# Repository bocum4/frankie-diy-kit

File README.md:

# frankie-diy-kit
Related hardware and building files. 

NOTA IMPORTANTE:

LIMITACIÓN DE GARANTÍA.

Este es un proyecto de dificultad media a avanzada. Se sugiere encarecidamente el previo conocimiento en el código de resistencias y otros elementos electrónicos así como experiencia soldando con cautín y soldadura de estaño. Bocuma no se responsabiliza por cualquier daño personal o material, defecto o malfunción derivada del incorrecto ensamble del kit.

Si tuviste problemas al armar tu kit y este no funciona después de haberlo ensamblado y verificado la guia de ensamble y guía de usuario, podremos asesorarte sin costo siempre y cuando esta revisión se realice durante los 30 días naturales siguientes a la fecha de tu compra. Transcurrido este lapso de tiempo las revisiones incurren en honorarios y están sujetas a nuestra disponibilidad y según nuestra carga de trabajo. Ponte en contacto con nosotros en contacto@bocuma.mx 

Todos nuestros kits están garantizados por nuestros proveedores, si por alguna razón algún componente de tu kit presenta una falla de fábrica lo reemplazaremos sin costo, para ello requeriremos que nos envies el componente o pieza defectuosa. Esta garantía tiene validez hasta por 3 meses después de la fecha de tu compra. Ponte en contacto con nosotros en contacto@bocuma.mx y te guiaremos en el proceso.

En caso de que a tu kit le falte una pieza o la hayas extraviado, puedes contactarnos en contacto@bocuma.mx y con gusto nos pondremos de acuerdo contigo para su reposición. Esta garantía tiene validez hasta por 3 meses después de la fecha de tu compra.

HACIA NUEVOS UNIVERSOS SONOROS | BOCUMA GDL MX 2021.

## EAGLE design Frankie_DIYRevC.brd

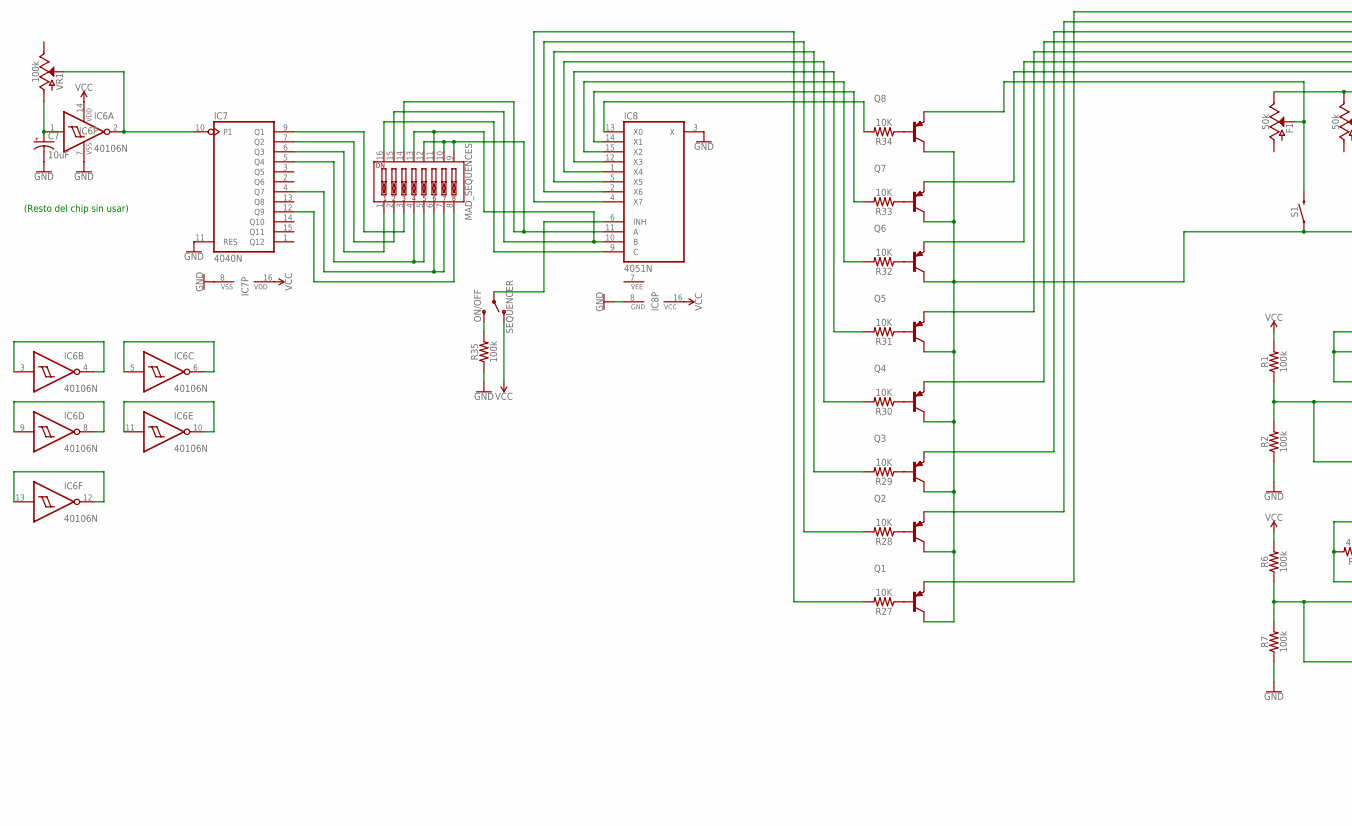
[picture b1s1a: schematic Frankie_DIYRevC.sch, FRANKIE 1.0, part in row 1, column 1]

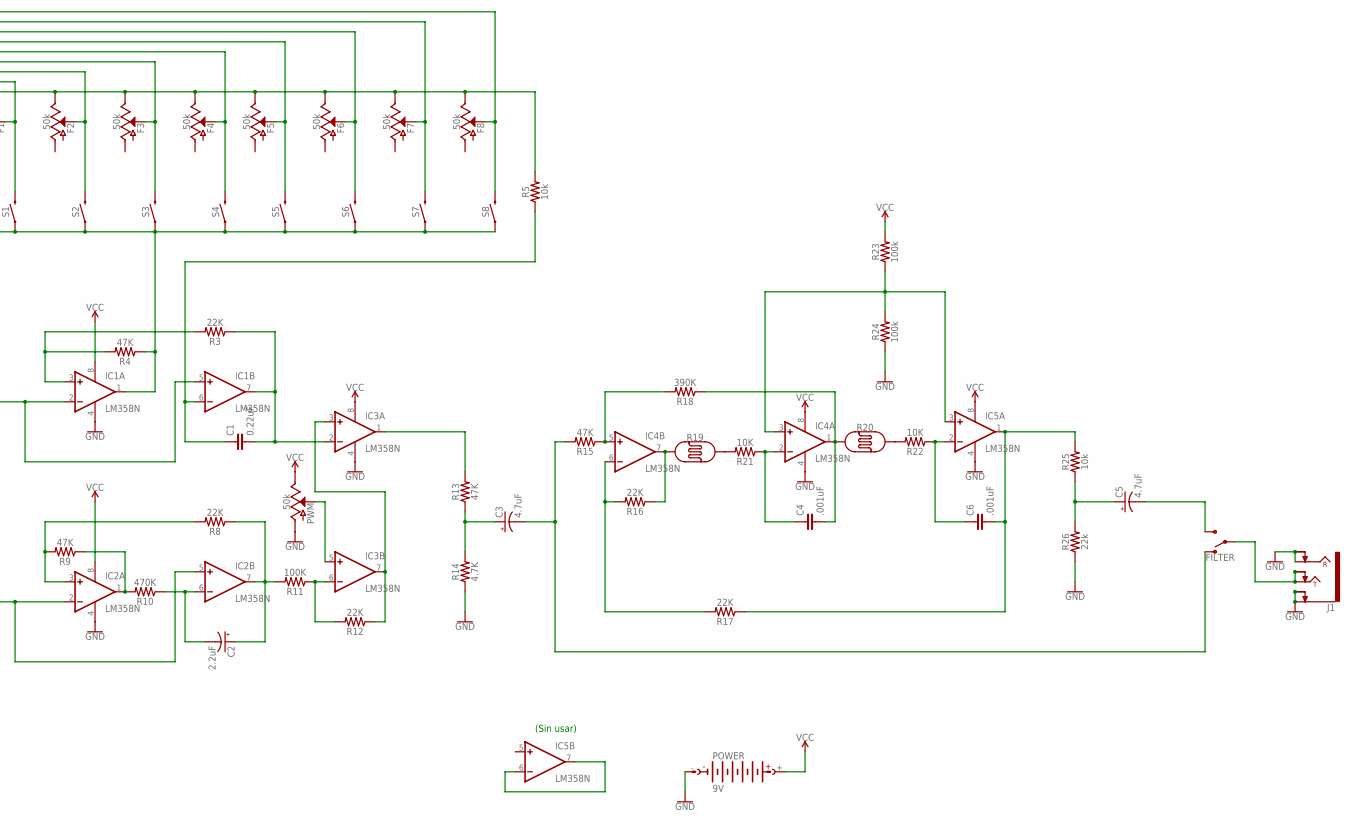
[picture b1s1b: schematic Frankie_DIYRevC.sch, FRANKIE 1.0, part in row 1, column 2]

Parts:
C1: 0.22uF; C5B2.5
C2: 2.2uF; CPOL-RADIAL-2.5MM-5MM-KIT
C3, C5: 4.7uF; CPOL-RADIAL-2.5MM-5MM-KIT
C4, C6: .001uF; C5B2.5
C7: 10uF; CPOL-RADIAL-2.5MM-5MM-KIT
F1, F2, F3, F4, F5, F6, F7, F8: 50k; POT-PTH-ALPS-KIT
FILTER: SWITCH-SPDT-PTH-11.6X4.0MM-KIT; SWITCH_SPDT_PTH_11.6X4.0MM_KIT
IC1, IC2, IC3, IC4, IC5: LM358N; DIL08
IC6: 40106N; DIL14
IC7: 4040N; DIL16
IC8: 4051N; DIL16
J1: AUDIO_JACK_TRS_0.25"_PTH_RA; AUDIO_JACK_0.25"_TRS_PTH_RA
MAD_SEQUENCES: DIP-08-PTH; DIPSWITCH-08
POWER: 9V; AB9V
PWM: 50k; POT-PTH-ALPS-KIT
Q1, Q2, Q3, Q4, Q5, Q6, Q7, Q8: 2N3906; TO92
R1, R2, R6, R7, R23, R24, R35: 100k; AXIAL-0.3
R3, R8, R12, R16, R17: 22K; AXIAL-0.3
R4, R9, R13, R15: 47K; AXIAL-0.3
R5, R25: 10k; AXIAL-0.3
R10: 470K; AXIAL-0.3
R11: 100K; AXIAL-0.3
R14: 4.7K; AXIAL-0.3
R18: 390K; AXIAL-0.3
R19, R20: PHOTOCELLPTH-KIT; PHOTOCELL-KIT
R21, R22, R27, R28, R29, R30, R31, R32, R33, R34: 10K; AXIAL-0.3
R26: 22k; AXIAL-0.3
S1, S2, S3, S4, S5, S6, S7, S8: MOMENTARY-SWITCH-SPST-PTH-12MM; TACTILE_SWITCH_PTH_12MM
SEQUENCER: ON/OFF; SWITCH_SPDT_PTH_11.6X4.0MM_KIT
VR1: 100k; POT-PTH-ALPS-KIT

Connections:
GND: C7.2 (-), IC1.4 (V-), IC2.4 (V-), IC3.4 (V-), IC4.4 (V-), IC5.4 (V-), IC6.7 (VSS), IC7.8 (VSS), IC7.11 (RES), IC8.3 (X), IC8.8 (GND), J1.RING, J1.RING-NORM, J1.SLEEVE (EARTH), J1.SLEEVE-NORM (EARTH-NORM), POWER.-, PWM.P$3 (A), R2.P$1 (1), R7.P$1 (1), R14.P$1 (1), R24.P$1 (1), R26.P$1 (1), R35.P$1 (1)
unnamed: IC1.2 (-IN), IC1.5 (+IN), R1.P$1 (1), R2.P$2 (2)
unnamed: C1.2, IC1.7 (OUT), IC3.2 (-IN), R3.P$1 (1)
unnamed: IC1.3 (+IN), R3.P$2 (2), R4.P$2 (2)
unnamed: C1.1, IC1.6 (-IN), R5.P$1 (1)
unnamed: IC1.1 (OUT), Q1.1 (C), Q2.1 (C), Q3.1 (C), Q4.1 (C), Q5.1 (C), Q6.1 (C), Q7.1 (C), Q8.1 (C), R4.P$1 (1), S1.1, S2.1, S3.1, S4.1, S5.1, S6.1, S7.1, S8.1
unnamed: F1.P$2 (S), Q8.3 (E), S1.3 (2)
unnamed: F2.P$2 (S), Q7.3 (E), S2.3 (2)
unnamed: IC7.5 (Q4), MAD_SEQUENCES.4, MAD_SEQUENCES.5
unnamed: F4.P$2 (S), Q5.3 (E), S4.3 (2)
unnamed: F5.P$2 (S), Q4.3 (E), S5.3 (2)
unnamed: F6.P$2 (S), Q3.3 (E), S6.3 (2)
unnamed: F7.P$2 (S), Q2.3 (E), S7.3 (2)
unnamed: F8.P$2 (S), Q1.3 (E), S8.3 (2)
unnamed: F1.P$1 (E), F2.P$1 (E), F3.P$1 (E), F4.P$1 (E), F5.P$1 (E), F6.P$1 (E), F7.P$1 (E), F8.P$1 (E), R5.P$2 (2)
unnamed: IC2.2 (-IN), IC2.5 (+IN), R6.P$1 (1), R7.P$2 (2)
unnamed: IC2.3 (+IN), R8.P$2 (2), R9.P$2 (2)
unnamed: IC2.1 (OUT), R9.P$1 (1), R10.P$2 (2)
unnamed: C2.2 (-), IC2.6 (-IN), R10.P$1 (1)
unnamed: IC3.6 (-IN), R11.P$1 (1), R12.P$2 (2)
unnamed: C2.1 (+), IC2.7 (OUT), R8.P$1 (1), R11.P$2 (2)
unnamed: IC3.5 (+IN), PWM.P$2 (S)
unnamed: IC3.3 (+IN), IC3.7 (OUT), R12.P$1 (1)
unnamed: IC3.1 (OUT), R13.P$2 (2)
unnamed: C3.1 (+), R13.P$1 (1), R14.P$2 (2)
unnamed: IC4.5 (+IN), R15.P$1 (1), R18.P$2 (2)
unnamed: C3.2 (-), FILTER.1 (O), R15.P$2 (2)
unnamed: IC4.6 (-IN), R16.P$2 (2), R17.P$2 (2)
unnamed: IC4.7 (OUT), R16.P$1 (1), R19.1
unnamed: C6.2, IC5.1 (OUT), R17.P$1 (1), R25.P$2 (2)
unnamed: C4.2, IC4.1 (OUT), R18.P$1 (1), R20.1
unnamed: R19.2, R21.P$2 (2)
unnamed: R20.2, R22.P$2 (2)
unnamed: C4.1, IC4.2 (-IN), R21.P$1 (1)
unnamed: C6.1, IC5.2 (-IN), R22.P$1 (1)
unnamed: IC5.6 (-IN), IC5.7 (OUT)
unnamed: IC4.3 (+IN), IC5.3 (+IN), R23.P$1 (1), R24.P$2 (2)
unnamed: C5.1 (+), R25.P$1 (1), R26.P$2 (2)
unnamed: FILTER.2, J1.TIP, J1.TIP-NORM
unnamed: Q1.2 (B), R27.P$1 (1)
unnamed: C5.2 (-), FILTER.3 (S)
unnamed: Q2.2 (B), R28.P$1 (1)
unnamed: Q3.2 (B), R29.P$1 (1)
unnamed: Q4.2 (B), R30.P$1 (1)
unnamed: Q5.2 (B), R31.P$1 (1)
unnamed: Q6.2 (B), R32.P$1 (1)
unnamed: Q7.2 (B), R33.P$1 (1)
unnamed: Q8.2 (B), R34.P$1 (1)
unnamed: C7.1 (+), IC6.1 (I), VR1.P$3 (A)
unnamed: IC6.2 (O), IC7.10 (P1), VR1.P$2 (S)
unnamed: IC7.9 (Q1), MAD_SEQUENCES.3
unnamed: IC7.12 (Q9), MAD_SEQUENCES.8
unnamed: IC7.6 (Q3), MAD_SEQUENCES.1
unnamed: IC8.11 (A), MAD_SEQUENCES.9, MAD_SEQUENCES.10, MAD_SEQUENCES.12, MAD_SEQUENCES.14
unnamed: IC8.10 (B), MAD_SEQUENCES.11, MAD_SEQUENCES.13, MAD_SEQUENCES.15
unnamed: IC8.9 (C), MAD_SEQUENCES.16
unnamed: IC8.6 (INH), SEQUENCER.2
unnamed: R35.P$2 (2), SEQUENCER.3 (S)
unnamed: IC8.13 (X0), R34.P$2 (2)
unnamed: IC8.14 (X1), R33.P$2 (2)
unnamed: IC8.15 (X2), R32.P$2 (2)
unnamed: IC8.12 (X3), R31.P$2 (2)
unnamed: IC8.1 (X4), R30.P$2 (2)
unnamed: IC8.5 (X5), R29.P$2 (2)
unnamed: IC8.2 (X6), R28.P$2 (2)
unnamed: IC8.4 (X7), R27.P$2 (2)
unnamed: IC7.7 (Q2), MAD_SEQUENCES.2
unnamed: IC7.4 (Q7), MAD_SEQUENCES.6, MAD_SEQUENCES.7
unnamed: F3.P$2 (S), Q6.3 (E), S3.3 (2)
unnamed: IC6.3 (I), IC6.4 (O)
unnamed: IC6.5 (I), IC6.6 (O)
unnamed: IC6.8 (O), IC6.9 (I)
unnamed: IC6.10 (O), IC6.11 (I)
unnamed: IC6.12 (O), IC6.13 (I)
VCC: IC1.8 (V+), IC2.8 (V+), IC3.8 (V+), IC4.8 (V+), IC5.8 (V+), IC6.14 (VDD), IC7.16 (VDD), IC8.16 (VCC), POWER.+, PWM.P$1 (E), R1.P$2 (2), R6.P$2 (2), R23.P$2 (2), SEQUENCER.1 (O)
VEE: IC8.7 (VEE)

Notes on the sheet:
(Sin usar)
(Resto del chip sin usar)

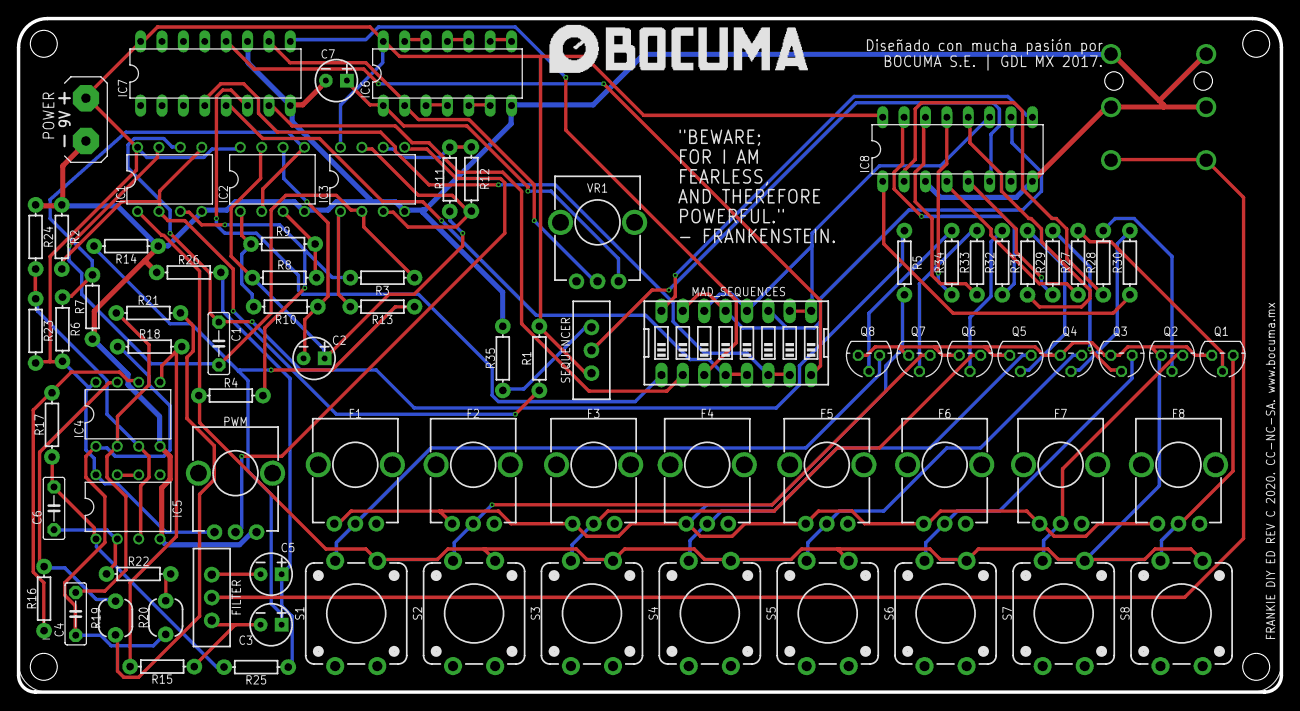
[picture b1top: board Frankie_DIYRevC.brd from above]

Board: 2 copper layers, 150.0 x 80.0 mm, 81 parts (1 on the bottom side), 75 nets.

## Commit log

2019-01-21 Added user manual.
    Added user instructions. PDF format.
2019-01-21 Add Bill Of Materials.
    Added bill of materials. Frankie DIY Ed. Rev A.
2019-01-21 Add schematic in pdf format.
    Frankie DIY REV A, pdf format.
2019-01-22 Update README.md
    NOTA IMPORTANTE.
2019-01-22 Add files via upload
    Archivo "LEEME"
    Notas importantes.
2019-01-25 Update EAGLE CAD files
2019-01-25 Add Papertoy
    Added a robosynth papertoy.
2019-03-04 Add files via upload
    Add Assembly Guide
2019-04-16 Add files via upload
    .stl files for 3D printing. Frankie Base.
2020-09-12 Update EAGLE Files
    Updated EAGLE design files for REV C, Latest revision.
2020-09-16 Update BOM
    Updated bill of materials for revision C
2020-09-18 Update BOM
    Updated Rev C Bill Of Materials
2020-11-15 Upload BOM duplicate
    Uploaded BOM duplicate with different name for documentation consistency.
2020-11-24 Update Frankie_AssemblyGuide.pdf
    Uploaded updated assembly guide with branding and graphic design enhancements.
2021-08-17 Add assembly guide and user manual in English

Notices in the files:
parts and their libraries:
SparkFun-Capacitors: Licensing: Creative Commons ShareAlike 4.0 International - https://creativecommons.org/licenses/by-sa/4.0
